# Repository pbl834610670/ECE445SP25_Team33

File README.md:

# ECE445SP25 Team33 Lab Notebook
Name: Ann Luo\
NetID: hluo12

## 05/05/2025
We had our final presentation today. Before the presentation, we made final adjustments to our PowerPoint slides, and I spent time at home practicing my part to ensure a smooth delivery. The presentation went well—we successfully presented our project and were able to answer the questions confidently. Through the progress we’ve made this semester, I’ve learned a lot, both technically and collaboratively. I’m proud of what we accomplished, and I believe I will continue working on this project beyond the course.

## 05/02/2025
We had our mock presentation today. Since we are still finalizing our PowerPoint, there are a few pictures and videos that still need to be added. During the presentation, the TAs provided us with helpful suggestions for improvement. One key takeaway was the need to explain each component of our subsystems in more detail. I plan to revise my part accordingly to ensure the explanations are clearer and more informative.

## 04/29/2025
We had our final demo today. In the morning, before the demonstration, we tested our robot car one last time and made a slight adjustment to the code by modifying a condition statement to better ensure the robot wouldn't fall off the table. We also gathered some dust from room 2070 to use during the demo and show the cleaning functionality. During the demo, one of our power supply wires broke, but we were able to quickly repair it and continue. In the end, we successfully completed the final demonstration. Additionally, we recorded a video of our table-cleaning robot as part of our preparation for the extra credit submission.

## 04/28/2025
Tomorrow is our final demo. During today’s testing, I realized that the code still needed some adjustments. I spent the evening refining it, and by the end of the night, the robot was operating smoothly on the table surface. I also noticed that for more reliable edge detection, the IR sensors needed to be positioned farther from the wheels to allow more response time. To address this, I attached two small cardboards to the front of the robot car and pasted the IR sensors on them. After further testing, I realized that making the robot car cover the entire table surface would be difficult to achieve within the limited time we have, due to constraints in the robot’s size and uncertainties on the table surface. Therefore, I decided to focus primarily on ensuring the obstacle avoidance and edge detection functionalities are reliable. I tested the robot’s functionality on a table at home, and it worked perfectly. However, I still need to confirm its performance on the lab table. The jack port for our PCB board has not yet arrived, so we’ll have to wait until tomorrow morning to test whether the PCB board can work.

## 04/27/2025
The file didn’t work as expected, so I bought a saw and brought the robot car home to remove the support pillars. Using the saw, I was finally able to lower the cooling fan to the proper height for effective dust collection. After that, I tested the code and discovered that the IR sensors weren’t properly adjusted. I used a screwdriver to fine-tune them so that both indicator lights turn on when detecting the table surface, and one light turns off when an edge is detected. I also realized that the wheels were rotating in the wrong direction, which caused the robot to behave incorrectly. I resolved this issue by correcting the motor wiring, and now the system functions properly.

## 04/25/2025
I assembled all the components onto the new model, and it worked perfectly. We were able to properly install the development board, battery, ultrasonic sensor, and IR sensors without any issues. However, after mounting the cooling fan, I noticed that it sits too far from the ground, which prevents it from effectively collecting dust. To address this, I decided to try using a file to shorten the three support pillars holding the fan, so it can sit closer to the surface and improve suction performance.

## 04/24/2025
To avoid material waste, we printed partial sections of our model to test whether the dimensions were accurate. After confirming the fit of the partial prints, we printed the full model in separate parts. Once all parts were printed, I planned to assemble them later into the complete structure.

## 04/23/2025
I spent time working on designing the 3D print model using Autodesk Fusion under with help from our TA. Interestingly, during this process, the robot car unexpectedly started working again. I'm not exactly sure what caused it to begin functioning, but it was a surprising and welcome outcome.

## 04/22/2025
We had our mock demo today and presented the robot car we built to our TA. Although the hardware was assembled, the car’s functionality is still not working, so we were unable to demonstrate the complete features.

## 04/21/2025
Our robot car suddenly stopped working. At first, I suspected the issue was due to a drained battery, so I purchased a new pair of batteries and replaced the old ones, but the car was still not working. I then began to consider the possibility that the motor driver might have burned out, so I ordered a replacement just in case. Since we plan to transition to a new model for our robot car, I’m also considering reassembling all the components onto the new model once it’s ready.

## 04/18/2025
I measured the dimensions of various parts of our robot car to prepare for building our own model. The vacuum fan measures 13 cm by 13 cm, which is a key constraint for our design. To ensure effective cleaning, the width of the robot car should be slightly larger than 13 cm but not exceed it by too much. I also purchased the appropriate screwdriver to dismantle parts from the machine shop’s model so they can be reused in our new version. Additionally, I completed the team contract assessment on Canvas.

## 04/16/2025
The machine shop finished building our robot car model and delivered it to us. However, the model turned out to be much larger than we expected. The most significant issue is that the width of the robot car is too wide—it greatly exceeds the coverage area of our vacuum fan. As a result, the cleaning subsystem cannot effectively cover the surface as the robot moves. To address this problem, I decided to create a new model that better fits the dimensions required for efficient cleaning.

## 04/08/2025
I’m still working on combining the obstacle avoidance and edge detection code to ensure both subsystems function smoothly together. After testing, I decided to switch from ultrasonic sensors to IR sensors for the edge detection subsystem, as IR sensors have faster response times and greater accuracy for detecting table edges. I ordered the IR sensors online and will begin assembling them on the robot car once they arrive.

## 04/05/2025
I worked on writing the code for the edge detection subsystem and began integrating it with the obstacle avoidance code. Further testing of the sensor readings is still needed to ensure smooth and successful integration. The logic may need to be adjusted to prevent any conflicts between the two subsystems.

## 04/02/2025
I completed the individual progress report today. In the report, I included a flow diagram that outlines the logic we plan to implement for our table-cleaning robot. Since one of our main goals is to ensure the robot can effectively cover the entire table surface, the diagram illustrates the detailed decision-making process and movement logic of our robot car.

## 04/01/2025
We first tested whether the voltage converter could successfully step up the voltage from 3.7V to 12V. After confirming it worked as expected, we connected one end of the converter to the battery and the other end to the vacuum fan. We then tested the functionality of the cooling fan to ensure it was able to effectively suck up dust from the table surface. In addition, we discussed the design of our robot’s base boards with the staff at the machine shop. During our discussion, a serious issue was brought up: since strong airflow is expelled from one of the cooling fan’s ports, using a plastic bin to collect dust would not work effectively. Bolin suggested an alternative solution which is using a sock instead of a bin. The sock would allow air to pass through while still being able to collect dust. I thought this was an excellent idea and a creative solution.

## 03/31/2025
We didn't place a PCB order during the third round due to issues we encountered while soldering our current board. Some of the pins were too closely spaced, which caused solder bridges and led to a short circuit on the board. Our team decided to focus on fixing this issue first.

## 03/26/2025
We assembled the electronic components for the obstacle avoidance subsystem and tested the code to verify its functionality. The system appears to be working well so far, but further adjustments may be necessary. This is because we still need to finalize and communicate our specific design requirements for the robot car to the machine shop, and wait for them to complete the final robot car model.

## 03/25/2025
I spent time researching various vacuum fan options for our debris collection subsystem, but most of them were unsuitable due to issues with voltage, size, or other limitations. After comparing several alternatives, I found a 12V computer cooling fan that might work for our needs and decided to purchase it for testing. Since our battery only supplies 3.7V, I also bought a voltage converter to ensure the fan receives the required power. Additionally, as we plan to solder our PCB in the coming days, I purchased soldering paste.

## 03/14/2025
We discussed our design with the machine shop and brought up the idea of incorporating a robotic arm into our obstacle avoidance subsystem. The goal was to lift objects and clean the area underneath them. However, they advised us against implementing this feature due to its complexity and feasibility. As a result, we decided to simplify the design and focus on detecting and avoiding obstacles.

## 03/13/2025
Today was the deadline for the second round of PCB orders. Initially, the machine shop informed us that the files we submitted were incomplete. However, I was able to send the correct and complete files just in time, and they were successfully accepted. As a result, we were able to place our PCB order before the deadline.

## 03/11/2025
We had our breadboard demo today. During the demo, we were able to demonstrate that our obstacle detection system works as intended. However, I realized that the presentation could have been more effective if we had connected the obstacle detection system directly to the robot car. This would have allowed us to better show how the robot responds to obstacles in real time, providing a clearer picture of the subsystem’s functionality.

## 03/10/2025
We now have a clear understanding of our circuit design. We successfully measured the distance between obstacles and our ultrasonic sensor and displayed the readings on the Arduino Uno serial monitor. However, since we are still in the process of assembling the system and want to avoid soldering wires directly onto our L293D motor driver at this stage, we decided not to connect the motors and ultrasonic sensor together.

## 03/06/2025
We completed the design document today, including finalizing the RV table and updating the visual aid. One of the major changes we made was replacing the depth camera with an ultrasonic sensor for obstacle avoidance, due to cost and compatibility concerns. Additionally, we switched our development board from the Raspberry Pi to the Arduino Uno to simplify our system. For the debris collection subsystem, we are still in the process of selecting a suitable vacuum fan. For now, we’ve included a 12V DC mini vacuum fan as a placeholder in the visual aid, but further research and testing are needed. We also updated our block diagram to ensure it accurately represents our current system design.

## 03/05/2025
I completed the teamwork evaluation today and continued working on assembling the breadboard. I focused on connecting the key components and verifying that the basic circuits function correctly.

## 03/04/2025
We signed up for the breadboard demo today and began working on our breadboard setup. We decided to start by building the robot car itself, focusing on assembling the motors and basic movement. At the same time, we also began implementing the obstacle avoidance functionality using an ultrasonic sensor.

## 03/03/2025
Today was the first round for PCB orders, but since we haven’t completed our PCB schematic yet, we plan to submit our order during the second round instead.

## 02/26/2025
I researched different options for the components we plan to use in each subsystem of our project. For each part, I compared different models to find the most suitable choices in terms of functionality, compatibility, and cost. To ensure that all components would work well together, especially in terms of voltage and current requirements, we carefully reviewed the datasheets of each component to avoid potential problem later in the development process.

## 02/21/2025
We met to discuss the components we will use for each subsystem of our project. Initially, we planned to use a depth camera for detecting the edges of the table. However, after deciding to use only the Arduino Uno as our development board and realizing that the depth camera is relatively expensive and may not be easily compatible，we decided to switch to using ultrasonic sensors for both obstacle avoidance and edge detection. 

## 02/19/2025
We had our design review demo today. Initially, we planned to use both a Raspberry Pi and an Arduino Uno as our development boards, with each handling different functionalities. For example, we intended for the ESP32 to control the robot car’s motion, while the Raspberry Pi would handle obstacle avoidance and edge detection. However, during the demo, we received feedback suggesting that we simplify the system by using only one development board. After discussing, we decided to use Arduino Uno as our primary development board.

## 02/14/2025
Today, we worked on drafting our team contract. We established expectations and ground rules to ensure effective communication throughout the project. Additionally, we assigned specific roles and responsibilities to each team member based on their strengths and interests.

## 02/13/2025
We finished writing our project proposal. We considered the details of each subsystem involved in our design and discussed the potential components we might use. We also evaluated different development boards to find out the one that best fits our project. I created the initial visual aid to help visualize our overall design. 

## 02/11/2025
We had our first group meeting this week, during which we discussed our goals and the tasks we need to complete for the rest of the semester. It gave us a clearer understanding of the project timeline. 

## 02/02/2025
Our project proposal was approved, and we officially finalized our project topic: Table Cleaning Robot – Autonomous Elevated Surface Cleaner.

## 01/29/2025
I submitted our initial project proposal to the course web board. After receiving feedback from the professor and TA, we made revisions based on their suggestions to improve the proposal.

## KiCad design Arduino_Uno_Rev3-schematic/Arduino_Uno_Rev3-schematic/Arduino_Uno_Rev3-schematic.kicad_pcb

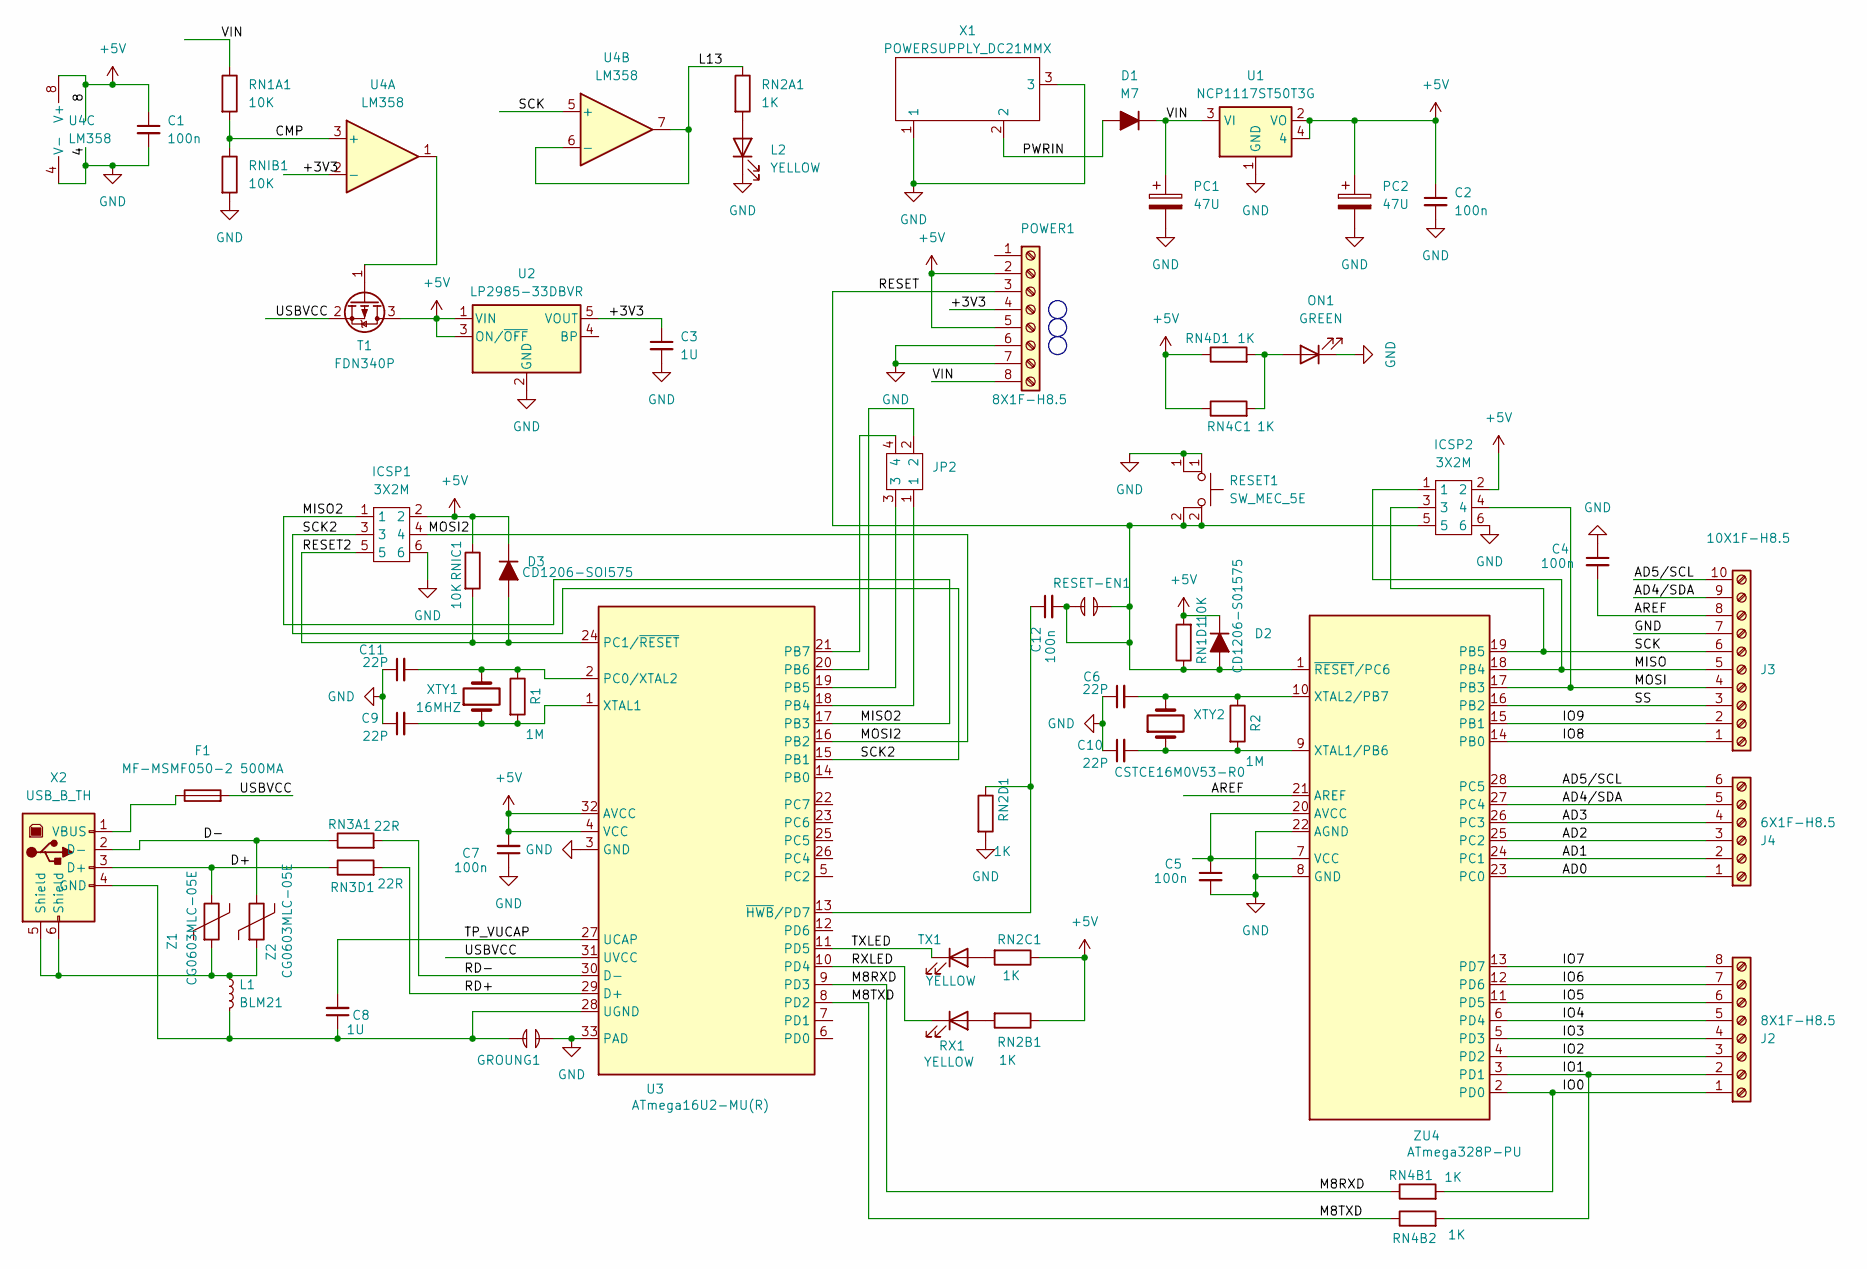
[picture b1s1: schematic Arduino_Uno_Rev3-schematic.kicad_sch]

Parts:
C1, C2, C4, C5, C7, C12: 100n; C_0603_1608Metric
C3, C8: 1U; C_0603_1608Metric
C6, C9, C10, C11: 22P; C_0603_1608Metric
D1: M7; SMA_L4.4-W2.8-LS5.4-RD
D2: CD1206-S01575; SMA_L4.4-W2.8-LS5.4-RD
D3: CD1206-SOI575; SMA_L4.4-W2.8-LS5.4-RD
F1: MF-MSMF050-2 500MA; F1206
GROUNG1: 1M; 短接焊盘111
ICSP1, ICSP2: 3X2M; HDR-F-2.54_2X3
J2: 8X1F-H8.5; HDR-F-2.54_1X8
J3: 10X1F-H8.5; HDR-F-2.54_1X10
J4: 6X1F-H8.5; HDR-F-2.54_1X6
JP2: HDR-M-2.54_2X2
L1: BLM21; L_0805_2012Metric
L2: YELLOW; LED_0603_1608Metric
ON1: GREEN; LED_0603_1608Metric
PC1, PC2: 47U; CAP-SMD_BD6.3-L6.6-W6.6-LS7.2-FD
POWER1: 8X1F-H8.5; HDR-F-2.54_1X8
R1, R2: 1M; R_0603_1608Metric
RESET1: SW_MEC_5E; SW-SMD_L3.9-W3.0-P4.45
RESET-EN1: 1M; 短接焊盘111
RN1A1, RN1D1: 10K; R_0603_1608Metric
RN2A1, RN2B1, RN2C1, RN2D1, RN4B1, RN4B2, RN4C1, RN4D1: 1K; R_0603_1608Metric
RN3A1, RN3D1: 22R; R_0603_1608Metric
RNIB1: 10K; R_0603_1608Metric
RNIC1: 10K; R_0603_1608Metric
RX1: YELLOW; LED_0603_1608Metric
T1: FDN340P; SOT-23
TX1: YELLOW; LED_0603_1608Metric
U1: NCP1117ST50T3G; SOT-223-3_TabPin2
U2: LP2985-33DBVR; SOT-23-5
U3: ATmega16U2-MU(R); QFN-32-1EP_5x5mm_P0.5mm_EP3.1x3.1mm
U4: LM358; SOIC-8_3.9x4.9mm_P1.27mm
X1: POWERSUPPLY_DC21MMX
X2: USB_B_TH; USB-B-TH_USB-B01
XTY1: 16MHZ; Crystal_SMD_HC49-SD
XTY2: CSTCE16M0V53-R0; OSC-SMD_3P-L3.2-W1.3-P0.95-L
Z1, Z2: CG0603MLC-05E; R_0603_1608Metric
ZU4: ATmega328P-PU; DIP-28_W7.62mm

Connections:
+5V: C1.1, C2.1, C7.2, D2.1 (K), D3.1 (K), ICSP1.2, ICSP2.2, PC2.1, POWER1.2, POWER1.5, RN1D1.2, RN2B1.1, RN2C1.1, RN4C1.1, RN4D1.1, RNIC1.1, T1.3 (D), U1.2 (VO), U1.4, U2.1 (VIN), U2.3 (ON/~OFF), U3.4 (VCC), U3.32 (AVCC), U4.8 (V+)
/+3V3: C3.1, POWER1.4, U2.5 (VOUT), U4.2 (-)
/AD0: J4.1, ZU4.23 (PC0)
/AD1: J4.2, ZU4.24 (PC1)
/AD2: J4.3, ZU4.25 (PC2)
/AD3: J4.4, ZU4.26 (PC3)
/AD4/SDA: J3.9, J4.5, ZU4.27 (PC4)
/AD5/SCL: J3.10, J4.6, ZU4.28 (PC5)
/AREF: C4.2, J3.8, ZU4.21 (AREF)
/CMP: RN1A1.2, RNIB1.1, U4.3 (+)
/D+: RN3D1.1, X2.3 (D+), Z1.1
/D-: RN3A1.1, X2.2 (D-), Z2.1
/IO0: J2.1, RN4B1.2, ZU4.2 (PD0)
/IO1: J2.2, RN4B2.2, ZU4.3 (PD1)
/IO2: J2.3, ZU4.4 (PD2)
/IO3: J2.4, ZU4.5 (PD3)
/IO4: J2.5, ZU4.6 (PD4)
/IO5: J2.6, ZU4.11 (PD5)
/IO6: J2.7, ZU4.12 (PD6)
/IO7: J2.8, ZU4.13 (PD7)
/IO8: J3.1, ZU4.14 (PB0)
/IO9: J3.2, ZU4.15 (PB1)
/L13: RN2A1.1, U4.6 (-), U4.7
/M8RXD: RN4B1.1, U3.9 (PD3)
/M8TXD: RN4B2.1, U3.8 (PD2)
/MISO: ICSP2.1, J3.5, ZU4.18 (PB4)
/MISO2: ICSP1.1, U3.17 (PB3)
/MOSI: ICSP2.4, J3.4, ZU4.17 (PB3)
/MOSI2: ICSP1.4, U3.16 (PB2)
/PWRIN: D1.2 (A), X1.2
/RD+: RN3D1.2, U3.29 (D+)
/RD-: RN3A1.2, U3.30 (D-)
/RESET: C12.2, D2.2 (A), ICSP2.5, POWER1.3, RESET1.2, RESET-EN1.1, RESET-EN1.2, RN1D1.1, ZU4.1 (~RESET/PC6)
/RESET2: D3.2 (A), ICSP1.5, RNIC1.2, U3.24 (PC1/~RESET)
/RXLED: RX1.1 (K), U3.10 (PD4)
/SCK: ICSP2.3, J3.6, U4.5 (+), ZU4.19 (PB5)
/SCK2: ICSP1.3, U3.15 (PB1)
/SS: J3.3, ZU4.16 (PB2)
/TP_VUCAP: C8.2, U3.27 (UCAP)
/TXLED: TX1.1 (K), U3.11 (PD5)
/USBVCC: F1.2, T1.2 (S), U3.31 (UVCC)
/VIN: D1.1 (K), PC1.1, POWER1.8, RN1A1.1, U1.3 (VI)
GND: C1.2, C2.2, C3.2, C4.1, C5.2, C6.1, C7.1, C9.1, C10.1, C11.1, GROUNG1.2, ICSP1.6, ICSP2.6, J3.7, L2.1 (K), ON1.1 (K), PC1.2, PC2.2, POWER1.6, POWER1.7, RESET1.1, RN2D1.2, RNIB1.2, U1.1 (GND), U2.2 (GND), U3.3 (GND), U3.33 (PAD), U4.4 (V-), X1.1, X1.3, ZU4.8 (GND), ZU4.22 (AGND)
unnamed: L1.1, X2.5 (Shield), X2.6 (Shield), Z1.2, Z2.2
unnamed: L2.2 (A), RN2A1.2
unnamed: ON1.2 (A), RN4C1.2, RN4D1.2
unnamed: RN2B1.2, RX1.2 (A)
unnamed: T1.1 (G), U4.1
unnamed: RN2C1.2, TX1.2 (A)
unnamed: JP2.1, U3.18 (PB4)
unnamed: JP2.3, U3.19 (PB5)
unnamed: JP2.2, U3.20 (PB6)
unnamed: JP2.4, U3.21 (PB7)
unnamed: C11.2, R1.1, U3.2 (PC0/XTAL2), XTY1.2
unnamed: C8.1, GROUNG1.1, L1.2, U3.28 (UGND), X2.4 (GND)
unnamed: C9.2, R1.2, U3.1 (XTAL1), XTY1.1
unnamed: C12.1, RN2D1.1, U3.13 (~HWB/PD7)
unnamed: F1.1, X2.1 (VBUS)
unnamed: C5.1, ZU4.7 (VCC), ZU4.20 (AVCC)
unnamed: C10.2, R2.2, XTY2.1, ZU4.9 (XTAL1/PB6)
unnamed: C6.2, R2.1, XTY2.3, ZU4.10 (XTAL2/PB7)

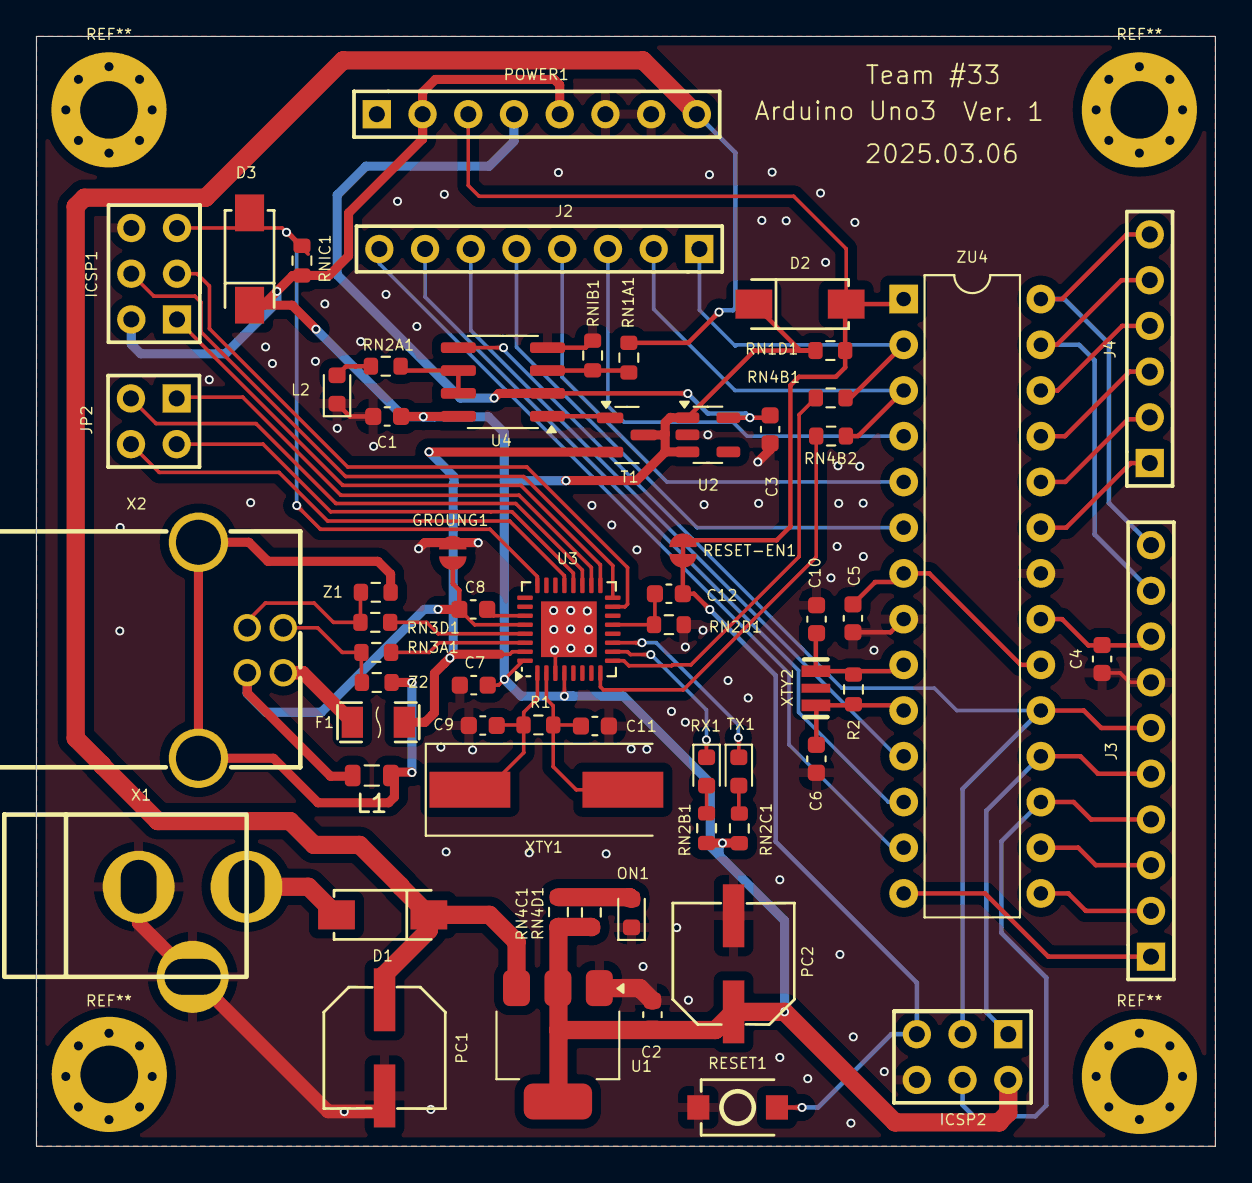
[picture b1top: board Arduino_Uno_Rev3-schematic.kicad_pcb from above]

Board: 2 copper layers, 65.5 x 61.7 mm, 61 parts (0 on the bottom side), 61 nets.

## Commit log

2025-04-02 Rename Obstacle Avoidance Schematic.jpg to Obstacle Avoidance Layout.jpg
2025-04-30 Create High-Level Requirements
2025-04-30 Update High-Level Requirements
2025-05-08 Add files via upload
    Breadboard demo code prototype
2025-05-08 Add files via upload
    Testing Motor
2025-05-08 Add files via upload
    Adafruit Library
2025-05-08 Add files via upload
    Combine obstacle avoidance system with edge detection system
2025-05-08 Add files via upload
    Final code
2025-05-08 Add files via upload
    Design document
2025-05-08 Create Ethical Considerations
